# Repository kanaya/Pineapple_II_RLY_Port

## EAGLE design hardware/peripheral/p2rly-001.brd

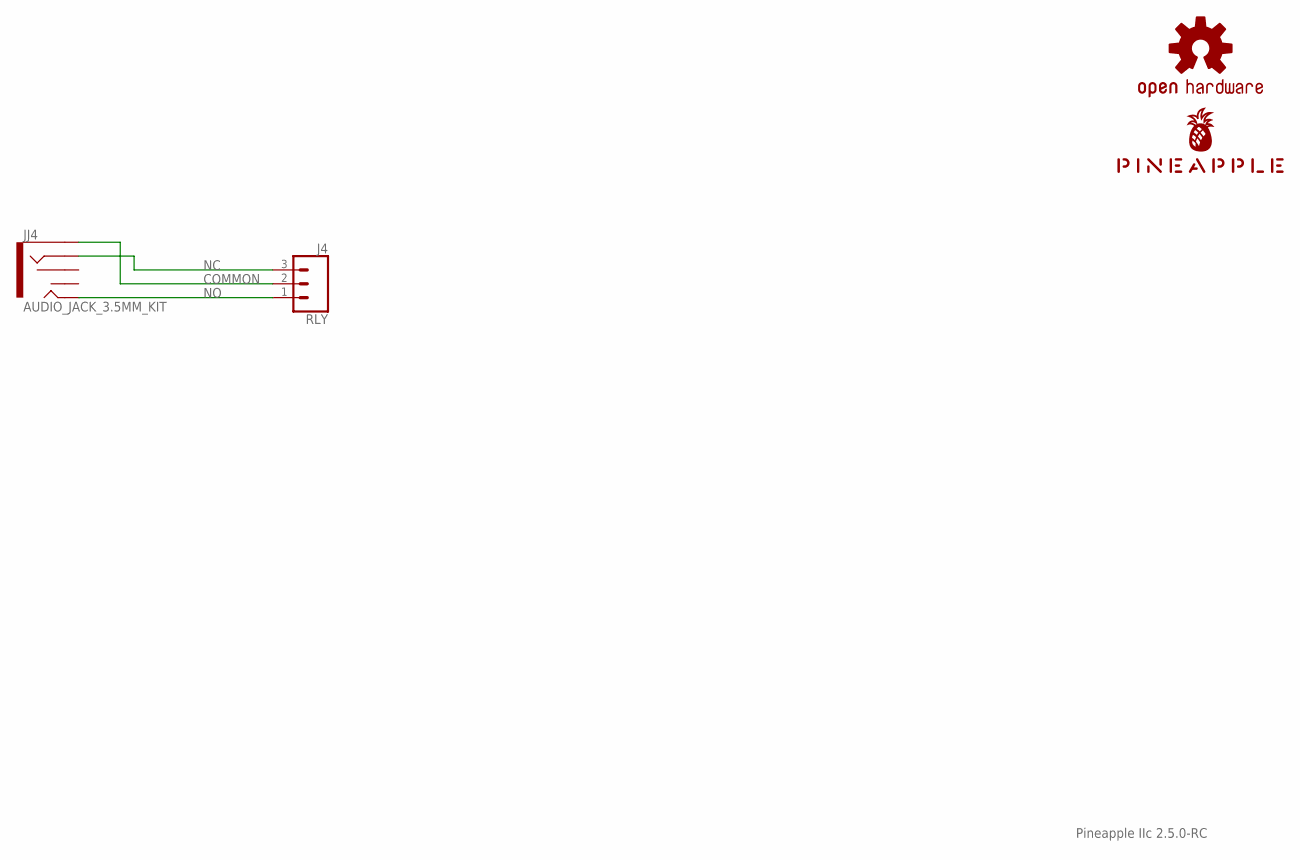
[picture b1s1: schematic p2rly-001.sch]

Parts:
J4: RLY; JST-3-PTH-VERT
JJ4: AUDIO_JACK_3.5MM_KIT; AUDIO-JACK-KIT
LOGO1: OSHW-LOGOS-COPPER; OSHW-LOGO-S_COPPER
U$1: PINEAPPLE450_SILK

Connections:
COMMON: J4.2, JJ4.SLEEVE
NC: J4.3, JJ4.RING
NO: J4.1, JJ4.TIP

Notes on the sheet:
Pineapple IIc 2.5.0-RC

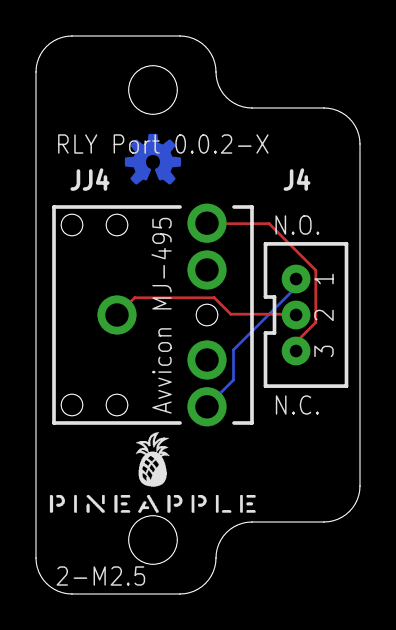
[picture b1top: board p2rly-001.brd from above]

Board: 2 copper layers, 18.0 x 31.0 mm, 4 parts (1 on the bottom side), 3 nets.

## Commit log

2022-08-16 Imported SCH and BRD from Pineapple II Hex Sw 0.0.2-X.
2022-09-13 Silk.
2022-10-14 Fixed polarity.

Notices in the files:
parts and their libraries:
SparkFun-Aesthetics: Licensing: Creative Commons ShareAlike 4.0 International - https://creativecommons.org/licenses/by-sa/4.0
